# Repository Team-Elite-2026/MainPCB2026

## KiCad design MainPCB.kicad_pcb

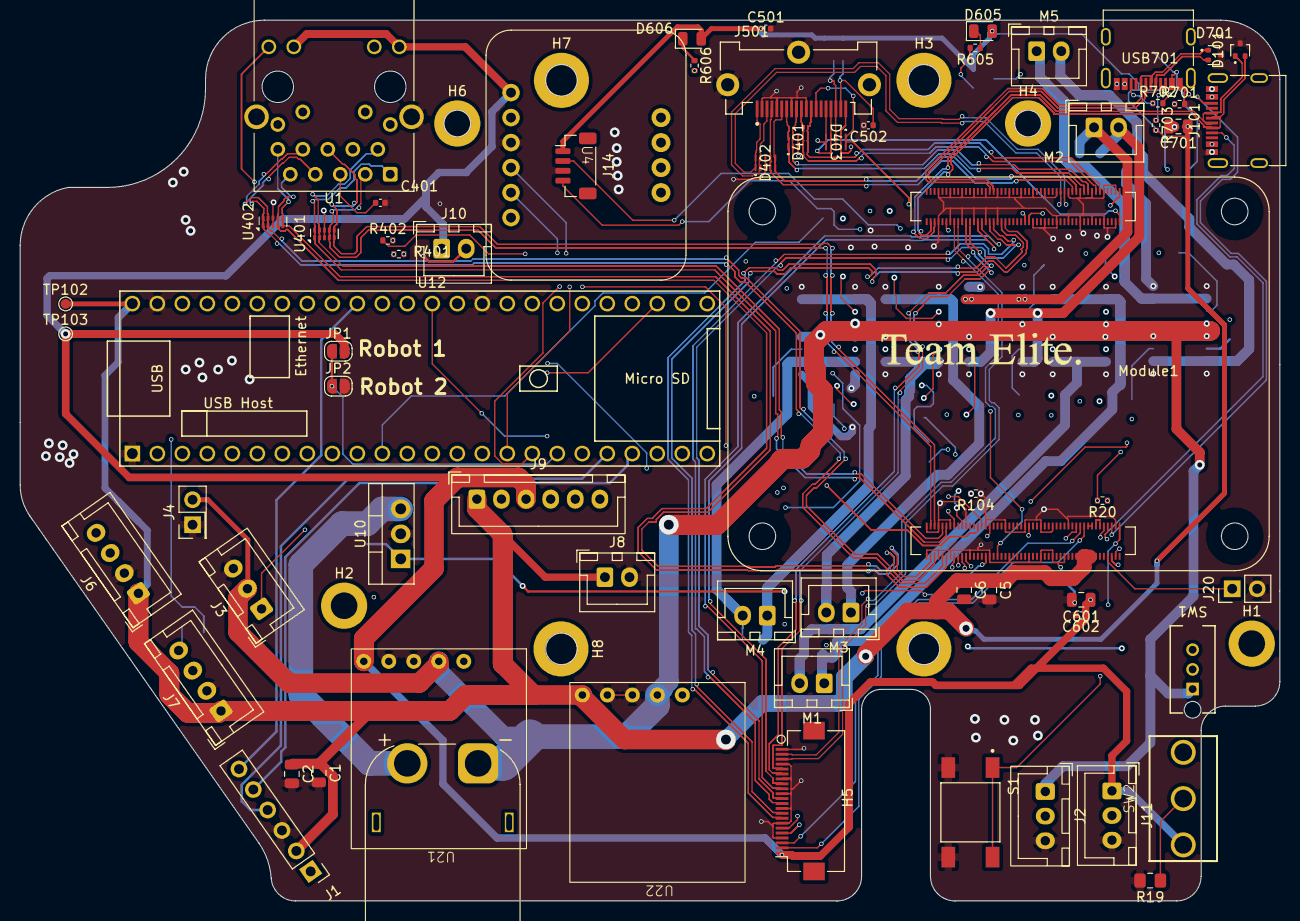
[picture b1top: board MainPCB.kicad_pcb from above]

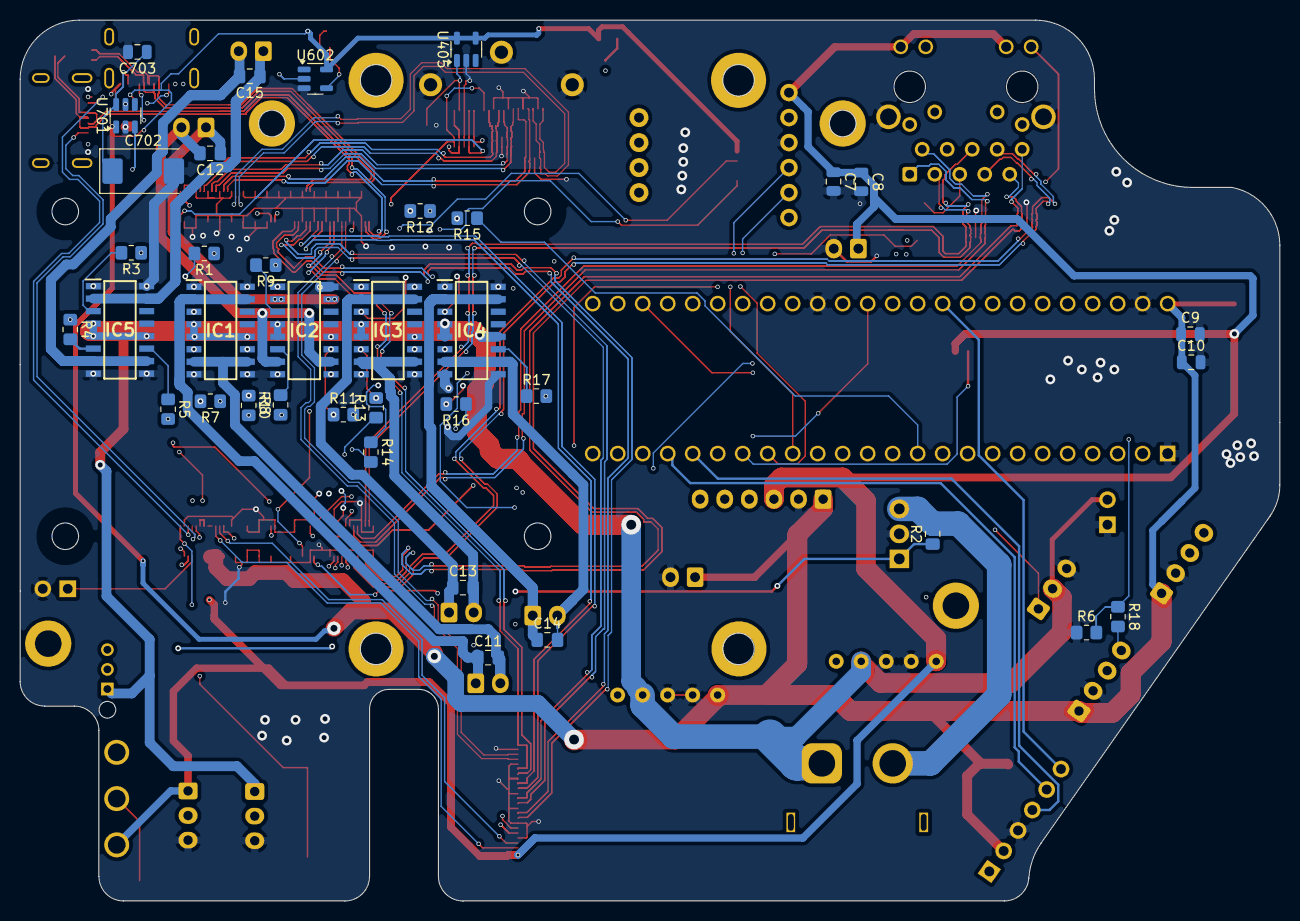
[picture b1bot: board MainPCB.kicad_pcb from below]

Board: 6 copper layers, 128.0 x 89.5 mm, 110 parts (37 on the bottom side), 131 nets.

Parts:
C1, C6, C8, C10: 10uf; C_0805_2012Metric
C2, C5, C7, C9: .1uf; C_0805_2012Metric
C11, C12, C13, C14, C15: 0.1uf; C_0805_2012Metric_Pad1.18x1.45mm_HandSolder
C401, C501, C502, C602: 100n; C_0402_1005Metric
C601: 4u7; C_0805_2012Metric
C701, C703: 10u; C_0805_2012Metric
C702: 100uF; CP_EIA-7343-31_Kemet-D
D101, D701: RCLAMP0502BA; SOT-416
D401, D402, D403: PUSB3F96X; DFN2510A-10_SOT1176-1_NEX
D605, D606: GREEN; D_0805_2012Metric
H1, H2, H4, H6: MountingHole; MountingHole_2.7mm_M2.5_DIN965_Pad
H3, H5, H7, H8: MountingHole; MountingHole_3.2mm_M3_DIN965_Pad
IC1, IC2, IC3, IC4, IC5: VNH7070ASTR; SOIC127P600X175-16N
J1: Conn_01x06; PinHeader_1x06_P2.54mm_Vertical
J2, J11: Conn_01x03; JST_XH_B3B-XH-A_1x03_P2.50mm_Vertical
J3: Conn_01x03_Pin; JST_XH_B3B-XH-A_1x03_P2.50mm_Vertical
J4: Conn_01x02; PinHeader_2x01_P2.54mm_Vertical
J5: Screw_Terminal_01x02; AMASS_XT60PW-M_1x02_P7.20mm_Horizontal
J6, J7: Conn_01x04_Pin; JST_XH_B4B-XH-A_1x04_P2.50mm_Vertical
J8, J10: Conn_01x02; JST_XH_B2B-XH-A_1x02_P2.50mm_Vertical
J9: Conn_01x06_Pin; JST_XH_B6B-XH-A_1x06_P2.50mm_Vertical
J14: JST_SHBM04B-SRSS-TB; JST_SH_BM04B-SRSS-TB_1x04-1MP_P1.00mm_Vertical
J20: Conn_01x02_Pin; PinHeader_1x02_P2.54mm_Vertical
J101: TYPEC-305-ACP16H458; USB_C_Receptacle_G-Switch_GT-USB-7010ASV
J501: GT-HD001B-CNNG1; PHOENIX_1332073
J802: Conn_01x22_Female; Hirose_FH12-22S-0.5SH_1x22-1MP_P0.50mm_Horizontal
JP1, JP2: SolderJumper_2_Open; SolderJumper-2_P1.3mm_Open_RoundedPad1.0x1.5mm
M1, M2, M3, M4, M5: Motor_DC; JST_XH_B2B-XH-A_1x02_P2.50mm_Vertical
Module1: ComputeModule5-CM5; Raspberry-Pi-5-Compute-Module
R1, R3, R4, R5, R7, R8, R9, R10, R11, R12, R13, R14, R15, R16, R17: 1k; R_0805_2012Metric_Pad1.20x1.40mm_HandSolder
R2, R19: 10k; C_0805_2012Metric_Pad1.18x1.45mm_HandSolder
R6: 3.3k; R_0805_2012Metric_Pad1.20x1.40mm_HandSolder
R18: 1.8k; R_0805_2012Metric_Pad1.20x1.40mm_HandSolder
R20: 10K 1%; R_0402_1005Metric
R104: 10k; R_0402_1005Metric
R401, R402: 470R; R_0402_1005Metric
R605, R606: 2k2; R_0402_1005Metric
R701: 15k; R_0402_1005Metric
R702, R703: 22k; R_0402_1005Metric
S1: TS04-66-70-BK-100-SMT; SW_TS04-66-70-BK-100-SMT
SW1: SW_DPST_x2; SPDT_OS102011_CNK
SW2: SW_DPST_x2; Latch-Switch
TP102: +5V_PI; TestPoint_Pad_D1.0mm
TP103: +3V3_PI; TestPoint_Pad_D1.0mm
U1: MagJack-A70-112-331N126; TRJG0926HENL
U4: BNO055
U10: N channel; TO-220-3_Vertical
U12: Teensy4.1; Teensy41
U21: V_Regulator3.3v; Pololu5V3.4A
U22: V_Regulator5v; Pololu5V3.4A
U401, U402: TPD4EUSB30; USON-10_2.5x1.0mm_P0.5mm
U405: STMPS2151STR; SOT-23-5
U602: SN74LVC1G14DBVR; SOT-23-5
U701: AP22653W6; SOT-23-6
USB701: TYPEC-305-ACP16H458; USB_C_Receptacle_G-Switch_GT-USB-7010ASV

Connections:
3.3V: C7.1, C8.1, C601.1, C602.1, J9.3, J10.1, J11.1, J802.22, JP1.2 (B), Module1.78 (GPIO_VREF(1.8v/3.3v_Input)), R20.1, SW2.1 (A), TP103.1 (1_1), U1.15 (LEDY_A), U1.17 (LEDG_A), U4.5 (VIN), U21.5 (OUT+)
5V: C1.1, C2.1, C5.1, C6.1, C9.1, C10.1, C501.1, C701.1, D605.2 (A), D606.2 (A), J1.2, J6.1, J7.1, J8.1, J9.1, J14.1, Module1.77 (+5v_(Input)), Module1.79 (+5v_(Input)), Module1.81 (+5v_(Input)), Module1.83 (+5v_(Input)), Module1.85 (+5v_(Input)), Module1.87 (+5v_(Input)), R702.2, R703.2, TP102.1 (1_1), U12.48 (VIN), U22.5 (OUT+), U405.4 (EN), U405.5 (VIN), U602.5 (VCC), U701.1 (IN)
12V: IC1.4 (VCC_1), IC1.5 (VCC_2), IC1.12 (VCC_3), IC2.4 (VCC_1), IC2.5 (VCC_2), IC2.12 (VCC_3), IC3.4 (VCC_1), IC3.5 (VCC_2), IC3.12 (VCC_3), IC4.4 (VCC_1), IC4.5 (VCC_2), IC4.12 (VCC_3), IC5.4 (VCC_1), IC5.5 (VCC_2), IC5.12 (VCC_3), J2.1, J3.2, J4.2, J5.1, SW1.1 (A), U21.3 (IN+), U22.3 (IN+)
+1V8: Module1.88 (+1.8v_(Output)), Module1.90 (+1.8v_(Output))
/CC1: J101.A5 (CC1), Module1.94 (CC1)
/CC2: J101.B5 (CC2), Module1.96 (CC2)
/CM5/3V3_CM4: Module1.84 (+3.3v_(Output)), Module1.86 (+3.3v_(Output))
/CM5/CAM_GPIO0: J802.17, Module1.97 (CAM_GPIO0)
/CM5/CAM_GPIO1: J802.18, Module1.100 (CAM_GPIO1)
/CM5/DPHY0_P.C_N: J802.8, Module1.127 (MIPI0_C_N)
/CM5/DPHY0_P.C_P: J802.9, Module1.129 (MIPI0_C_P)
/CM5/DPHY0_P.D0_N: J802.2, Module1.115 (MIPI0_D0_N)
/CM5/DPHY0_P.D0_P: J802.3, Module1.117 (MIPI0_D0_P)
/CM5/DPHY0_P.D1_N: J802.5, Module1.121 (MIPI0_D1_N)
/CM5/DPHY0_P.D1_P: J802.6, Module1.123 (MIPI0_D1_P)
/CM5/DPHY0_P.D2_N: J802.11, Module1.133 (MIPI0_D2_N)
/CM5/DPHY0_P.D2_P: J802.12, Module1.135 (MIPI0_D2_P)
/CM5/DPHY0_P.D3_N: J802.14, Module1.139 (MIPI0_D3_N)
/CM5/DPHY0_P.D3_P: J802.15, Module1.141 (MIPI0_D3_P)
/CM5/EEPROM_nWP: Module1.20 (EEPROM_nWP), R104.2
/CM5/ETH_PI.TRD0_N: Module1.10 (Ethernet_Pair0_N), U1.2 (TRD0-), U401.2 (D1-), U401.9
/CM5/ETH_PI.TRD0_P: Module1.12 (Ethernet_Pair0_P), U1.1 (TRD0+), U401.1 (D1+), U401.10
/CM5/ETH_PI.TRD1_N: Module1.6 (Ethernet_Pair1_N), U1.6 (TRD1-), U401.5 (D2-), U401.6
/CM5/ETH_PI.TRD1_P: Module1.4 (Ethernet_Pair1_P), U1.3 (TRD1+), U401.4 (D2+), U401.7
/CM5/ETH_PI.TRD2_N: Module1.9 (Ethernet_Pair2_N), U1.8 (TRD2-), U402.2 (D1-), U402.9
/CM5/ETH_PI.TRD2_P: Module1.11 (Ethernet_Pair2_P), U1.7 (TRD2+), U402.1 (D1+), U402.10
/CM5/ETH_PI.TRD3_N: Module1.5 (Ethernet_Pair3_N), U1.10 (TRD3-), U402.5 (D2-), U402.6
/CM5/ETH_PI.TRD3_P: Module1.3 (Ethernet_Pair3_P), U1.9 (TRD3+), U402.4 (D2+), U402.7
/CM5/ETH_nLED_ACTIVITY: Module1.15 (Ethernet_nLED3(3.3v)), R401.1
/CM5/HDMI_PI.CEC: D403.1 (CH1), D403.10 (NC), J501.13 (CEC), Module1.151 (HDMI0_CEC)
/CM5/HDMI_PI.CK_N: D401.5 (CH4), D401.6 (NC), J501.12 (CK-), Module1.190 (HDMI0_CLK_N)
/CM5/HDMI_PI.CK_P: D401.4 (CH3), D401.7 (NC), J501.10 (CK+), Module1.188 (HDMI0_CLK_P)
/CM5/HDMI_PI.D0_N: D401.2 (CH2), D401.9 (NC), J501.9 (D0-), Module1.184 (HDMI0_TX0_N)
/CM5/HDMI_PI.D0_P: D401.1 (CH1), D401.10 (NC), J501.7 (D0+), Module1.182 (HDMI0_TX0_P)
/CM5/HDMI_PI.D1_N: D402.5 (CH4), D402.6 (NC), J501.6 (D1-), Module1.178 (HDMI0_TX1_N)
/CM5/HDMI_PI.D1_P: D402.4 (CH3), D402.7 (NC), J501.4 (D1+), Module1.176 (HDMI0_TX1_P)
/CM5/HDMI_PI.D2_N: D402.2 (CH2), D402.9 (NC), J501.3 (D2-), Module1.172 (HDMI0_TX2_N)
/CM5/HDMI_PI.D2_P: D402.1 (CH1), D402.10 (NC), J501.1 (D2+), Module1.170 (HDMI0_TX2_P)
/CM5/HDMI_PI.HOTPLUG: D403.2 (CH2), D403.9 (NC), J501.19 (HPD/HEAC-), Module1.153 (HDMI0_HOTPLUG)
/CM5/HDMI_PI.SCL: D403.5 (CH4), D403.6 (NC), J501.15 (SCL), Module1.200 (HDMI0_SCL)
/CM5/HDMI_PI.SDA: D403.4 (CH3), D403.7 (NC), J501.16 (SDA), Module1.199 (HDMI0_SDA)
/CM5/PI_nLED_PWR: Module1.95 (LED_nPWR), U602.2
/CM5/PWM: J14.2, Module1.19 (FAN_PWM), R20.2
/CM5/PWR_BUT: Module1.92 (PWR_BUT), S1.1, S1.3
/CM5/TACHO: J14.4, Module1.16 (FAN_TACHO)
/CM5/USB2P.D_N: D701.2 (K2), Module1.136 (USB3-0-D_N), USB701.A7 (D-), USB701.B7 (D-)
/CM5/USB2P.D_P: D701.1 (K1), Module1.134 (USB3-0-D_P), USB701.A6 (D+), USB701.B6 (D+)
/CM5/VBUS_EN: Module1.111 (VBUS_EN), U701.3 (EN)
/CM5/nLED_ACTIVITY: Module1.21 (LED_nACT), R606.2
/CM5/nLED_SPEED_100_1000: Module1.17 (Ethernet_nLED2(3.3v)), R402.1
/CM5/nRPIBOOT: J20.1, Module1.93 (nRPIBOOT)
/SCL: J802.20, Module1.80 (SCL0)
/SDA: J802.21, Module1.82 (SDA0)
/USB/CC1: R703.1, USB701.A5 (CC1)
/USB/CC2: R702.1, USB701.B5 (CC2)
/USB_C.D_N: D101.2 (K2), J101.A7 (D-), J101.B7 (D-), Module1.103 (USB2_N)
/USB_C.D_P: D101.1 (K1), J101.A6 (D+), J101.B6 (D+), Module1.105 (USB2_P)
CommModuleRun: J2.2, U12.19 (27_A13_SCK1)
DIR1A: R1.1, U12.44 (22_A8_CTX1)
DIR1B: R7.1, U12.45 (23_A9_CRX1_MCLK1)
DIR2A: R9.1, U12.42 (20_A6_TX5_LRCLK1)
DIR2B: R10.1, U12.43 (21_A7_RX5_BCLK1)
DIR3A: R12.1, U12.40 (18_A4_SDA)
DIR3B: R13.1, U12.23 (31_CTX3)
DIR4A: R15.1, U12.11 (9_OUT1C)
DIR4B: R16.1, U12.12 (10_CS_MQSR)
DIR5A: R3.1, U12.13 (11_MOSI_CTX1)
DIR5B: R4.1, U12.14 (12_MISO_MQSL)
GND: C1.2, C2.2, C5.2, C6.2, C7.2, C8.2, C9.2, C10.2, C401.2, C501.2, C502.2, C601.2, C602.2, C701.2, C702.2, C703.2, D101.3 (A), D401.3 (GND), D401.8 (GND), D402.3 (GND), D402.8 (GND), D403.3 (GND), D403.8 (GND), D701.3 (A), IC1.1 (GND_A_1), IC1.8 (GND_B_1), IC1.9 (GND_B_2), IC1.16 (GND_A_2), IC2.1 (GND_A_1), IC2.8 (GND_B_1), IC2.9 (GND_B_2), IC2.16 (GND_A_2), IC3.1 (GND_A_1), IC3.8 (GND_B_1), IC3.9 (GND_B_2), IC3.16 (GND_A_2), IC4.1 (GND_A_1), IC4.8 (GND_B_1), IC4.9 (GND_B_2), IC4.16 (GND_A_2), IC5.1 (GND_A_1), IC5.8 (GND_B_1), IC5.9 (GND_B_2), IC5.16 (GND_A_2), J1.3, J2.3, J3.3, J4.1, J6.2, J7.2, J8.2, J9.2, J10.2, J11.3, J14.3, J20.2, J101.A1 (GND), J101.A12 (GND), J101.B1 (GND), J101.B12 (GND), J501.2 (D2S), J501.5 (D1S), J501.8 (D0S), J501.11 (CKS), J501.17 (GND), J501.SH1 (SH), J501.SH2 (SH), J501.SH3 (SH), J802.1, J802.4, J802.7, J802.10, J802.13, J802.16, J802.19, JP2.2 (B), Module1.1 (GND), Module1.2 (GND), Module1.7 (GND), Module1.8 (GND), Module1.13 (GND), Module1.14 (GND), Module1.22 (GND), Module1.23 (GND), Module1.32 (GND), Module1.33 (GND), Module1.42 (GND), Module1.43 (GND), Module1.52 (GND), Module1.53 (GND), Module1.59 (GND), Module1.60 (GND), Module1.65 (GND), Module1.66 (GND), Module1.71 (GND), Module1.74 (GND), Module1.98 (GND), Module1.107 (GND), Module1.108 (GND), Module1.113 (GND), Module1.114 (GND), Module1.119 (GND), Module1.120 (GND), Module1.125 (GND), Module1.126 (GND), Module1.131 (GND), Module1.132 (GND), Module1.137 (GND), Module1.138 (GND), Module1.144 (GND), Module1.150 (GND), Module1.155 (GND), Module1.156 (GND), Module1.161 (GND), Module1.162 (GND), Module1.167 (GND), Module1.168 (GND), Module1.173 (GND), Module1.174 (GND), Module1.179 (GND), Module1.180 (GND), Module1.185 (GND), Module1.186 (GND), Module1.191 (GND), Module1.192 (GND), Module1.197 (GND), Module1.198 (GND), R6.1, R19.2, R104.1, R701.2, S1.2, S1.4, U1.19 (SHIELD), U1.20 (SHIELD), U4.7 (GND), U10.2 (S), U12.1 (GND), U12.34 (GND), U12.47 (GND), U21.4 (OUT-), U22.4 (OUT-), U401.3 (GND), U401.8 (GND), U402.3 (GND), U402.8 (GND), U405.2 (GND), U602.3 (GND), U701.2 (GND), USB701.A1 (GND), USB701.A12 (GND), USB701.B1 (GND), USB701.B12 (GND)
HDMI_+5V: C502.1, J501.18 (+5V), U405.1 (VOUT)
Kicker: J3.1, U12.22 (30_CRX3)
LightGate: J11.2, U12.33 (41_A17)
unnamed: C401.1, U1.4 (CT), U1.5 (CT)
unnamed: D605.1 (K), R605.1
unnamed: D606.1 (K), R606.1
unnamed: IC1.3 (IN_A), R1.2
unnamed: IC1.6 (IN_B), R7.2
unnamed: C11.1, IC1.2 (OUT_A_1), IC1.15 (OUT_A_2), M1.1 (+)
unnamed: C11.2, IC1.7 (OUT_B_1), IC1.10 (OUT_B_2), M1.2 (-)
unnamed: IC1.11 (PWM), R8.1
unnamed: IC2.3 (IN_A), R9.2
unnamed: IC2.6 (IN_B), R10.2
unnamed: C12.1, IC2.2 (OUT_A_1), IC2.15 (OUT_A_2), M2.1 (+)
unnamed: C12.2, IC2.7 (OUT_B_1), IC2.10 (OUT_B_2), M2.2 (-)
unnamed: IC2.11 (PWM), R11.1
unnamed: IC3.3 (IN_A), R12.2
unnamed: IC3.6 (IN_B), R13.2
unnamed: C13.1, IC3.2 (OUT_A_1), IC3.15 (OUT_A_2), M3.1 (+)
unnamed: C13.2, IC3.7 (OUT_B_1), IC3.10 (OUT_B_2), M3.2 (-)
unnamed: IC3.11 (PWM), R14.1
unnamed: IC4.3 (IN_A), R15.2
unnamed: IC4.6 (IN_B), R16.2
unnamed: C14.1, IC4.2 (OUT_A_1), IC4.15 (OUT_A_2), M4.1 (+)
unnamed: C14.2, IC4.7 (OUT_B_1), IC4.10 (OUT_B_2), M4.2 (-)
unnamed: IC4.11 (PWM), R17.1
unnamed: IC5.3 (IN_A), R3.2
unnamed: IC5.6 (IN_B), R4.2
unnamed: C15.1, IC5.2 (OUT_A_1), IC5.15 (OUT_A_2), M5.1 (+)
unnamed: C15.2, IC5.7 (OUT_B_1), IC5.10 (OUT_B_2), M5.2 (-)
unnamed: IC5.11 (PWM), R5.1
unnamed: J5.2, R2.2, U10.3 (D)
unnamed: J7.4, R18.2
unnamed: J101.A4 (VBUS), J101.A9 (VBUS), J101.B4 (VBUS), J101.B9 (VBUS)
unnamed: R605.2, U602.4
unnamed: R2.1, SW1.2 (B), U10.1 (G)
unnamed: R401.2, U1.18 (LEDG_K)
unnamed: R402.2, U1.16 (LEDY_K)
unnamed: R701.1, U701.5 (ILIM)
PWM1: R8.2, U12.4 (2_OUT2)
PWM2: R11.2, U12.5 (3_LRCLK2)
PWM3: R14.2, U12.6 (4_BCLK2)
PWM4: R17.2, U12.7 (5_IN2)
PWM5: R5.2, U12.8 (6_OUT1D)
PWM-LIDAR: J6.3, Module1.31 (GPIO12)
RX3->TX: Module1.54 (GPIO4), U12.37 (15_A1_RX3_SPDIF_IN)
RX7 -> TX: J1.4, U12.20 (28_RX7)
RX8 -> TX: R6.2, R18.1, U12.26 (34_RX8)
RX(4.1)-TX(4.0): J9.5, U12.9 (7_RX2_OUT1A)
RX->TX - LIDAR: J6.4, Module1.28 (GPIO13)
SCL2: U4.8 (SCL), U12.16 (24_A10_TX6_SCL2)
SDA2: U4.9 (SDA), U12.17 (25_A11_RX6_SDA2)
STATE: J1.6, U12.39 (17_A3_TX4_SDA1)
SelectionPin: JP1.1 (A), JP2.1 (A), U12.18 (26_A12_MOSI1)
Start/Stop: R19.1, SW2.2 (B), U12.30 (38_CS1_IN1)
TX3->RX: Module1.34 (GPIO5), U12.36 (14_A0_TX3_SPDIF_OUT)
TX7 -> RX: J1.5, U12.21 (29_TX7)
TX8 -> RX: J7.3, U12.27 (35_TX8)
TX(4.1)-RX(4.0): J9.6, U12.10 (8_TX2_IN1)
UART3_CTS -> RTS: Module1.37 (GPIO7), U12.41 (19_A5_SCL)
UART3_RTS -> CTS: Module1.30 (GPIO6), U12.24 (32_OUT1B)
VBUS_USB2.0: C702.1, C703.1, U701.6 (OUT), USB701.A4 (VBUS), USB701.A9 (VBUS), USB701.B4 (VBUS), USB701.B9 (VBUS)

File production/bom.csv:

Designator,Footprint,Quantity,Value,LCSC Part #
"C1, C10, C6, C8",0805,4,10uf,
"C11, C12, C13, C14, C15",0805,5,0.1uf,
"C2, C5, C7, C9",0805,4,.1uf,
"C401, C501, C502, C602",0402,4,100n,
C601,0805,1,4u7,
"C701, C703",0805,2,10u,
C702,CP_EIA-7343-31_Kemet-D,1,100uF,
"D101, D701",SOT-416,2,RCLAMP0502BA,
"D401, D402, D403",DFN2510A-10_SOT1176-1_NEX,3,PUSB3F96X,C478121
"D605, D606",0805,2,GREEN,
"H3, H5, H7, H8",MountingHole_3.2mm_M3_DIN965_Pad,4,MountingHole,
"IC1, IC2, IC3, IC4, IC5",SOIC127P600X175-16N,5,VNH7070ASTR,
J1,PinHeader_1x06_P2.54mm_Vertical,1,Conn_01x06,
"J10, J8",JST_XH_B2B-XH-A_1x02_P2.50mm_Vertical,2,Conn_01x02,
J101,USB_C_Receptacle_G-Switch_GT-USB-7010ASV,1,TYPEC-305-ACP16H458,
"J11, J2",JST_XH_B3B-XH-A_1x03_P2.50mm_Vertical,2,Conn_01x03,
J14,JST_SH_BM04B-SRSS-TB_1x04-1MP_P1.00mm_Vertical,1,JST_SHBM04B-SRSS-TB,
J20,PinHeader_1x02_P2.54mm_Vertical,1,Conn_01x02_Pin,
J3,JST_XH_B3B-XH-A_1x03_P2.50mm_Vertical,1,Conn_01x03_Pin,
J4,PinHeader_2x01_P2.54mm_Vertical,1,Conn_01x02,
J5,AMASS_XT60PW-M_1x02_P7.20mm_Horizontal,1,Screw_Terminal_01x02,
J501,PHOENIX_1332073,1,GT-HD001B-CNNG1,
"J6, J7",JST_XH_B4B-XH-A_1x04_P2.50mm_Vertical,2,Conn_01x04_Pin,
J802,Hirose_FH12-22S-0.5SH_1x22-1MP_P0.50mm_Horizontal,1,Conn_01x22_Female,
J9,JST_XH_B6B-XH-A_1x06_P2.50mm_Vertical,1,Conn_01x06_Pin,
"M1, M2, M3, M4, M5",JST_XH_B2B-XH-A_1x02_P2.50mm_Vertical,5,Motor_DC,
MODULE1,Raspberry-Pi-5-Compute-Module,1,ComputeModule5-CM5,
"R1, R10, R11, R12, R13, R14, R15, R16, R17, R3, R4, R5, R7, R8, R9",0805,15,1k,
R104,0402,1,10k,
R18,0805,1,1.8k,
"R19, R2",0805,2,10k,
R20,0402,1,10K 1%,
"R401, R402",0402,2,470R,
R6,0805,1,3.3k,
"R605, R606",0402,2,2k2,
R701,0402,1,15k,
"R702, R703",0402,2,22k,
S1,SW_TS04-66-70-BK-100-SMT,1,TS04-66-70-BK-100-SMT,
SW1,SPDT_OS102011_CNK,1,SW_DPST_x2,
SW2,Latch-Switch,1,SW_DPST_x2,
U1,TRJG0926HENL,1,MagJack-A70-112-331N126,
U10,TO-220-3_Vertical,1,N channel,
U12,Teensy41,1,Teensy4.1,
U21,Pololu5V3.4A,1,V_Regulator3.3v,
U22,Pololu5V3.4A,1,V_Regulator5v,
U4,BNO055,1,BNO055,
"U401, U402",USON-10_2.5x1.0mm_P0.5mm,2,TPD4EUSB30,
U405,SOT-23-5,1,STMPS2151STR,C135998
U602,SOT-23-5,1,SN74LVC1G14DBVR,
U701,SOT-23-6,1,AP22653W6,
USB701,USB_C_Receptacle_G-Switch_GT-USB-7010ASV,1,TYPEC-305-ACP16H458,C5454943

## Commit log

2025-09-29 Main Starting
2025-10-10 Placement Done
2025-10-12 PCB Done
2026-03-22 Placed Everything for new version
2026-03-24 Finished Power Wiring and Fixed Schematic Bus Issues
2026-03-27 Finished Routing Diff Pairs
2026-03-27 Fixed some errors
2026-03-27 Did a bunch of routing, freerouting is broken, and im lowk tired
2026-03-28 Finished Routing
2026-03-30 Added LiDAR and LCD connections
2026-04-01 Finished Everything
2026-05-16 Stuff idk
2026-05-20 Added ground vias to each ground
2026-05-23 Added Changed for Line and Kicker PCB
    Still need to work out boost converter position
2026-05-25 Made Changes
2026-05-25 Added Voltage Dividers for UNO
2026-05-25 Not sending 12V to Line
2026-05-25 added pre-defined via sizes
2026-05-26 removed bad traces
2026-05-26 Added 3D Models
2026-05-26 Finished some routing
2026-05-27 Finished
2026-05-27 Finished 3D Model Rendering
2026-05-27 updated some traces
2026-05-27 Made changes to placement and HDMI is now vertical
2026-05-27 Moved Components and Fixed Placements
2026-05-29 Fixed Outline and moved around holes
2026-05-29 fixed drc errors
2026-05-29 Fixed Errors
2026-05-29 Added Connector for Fan
2026-05-30 Made some changes
